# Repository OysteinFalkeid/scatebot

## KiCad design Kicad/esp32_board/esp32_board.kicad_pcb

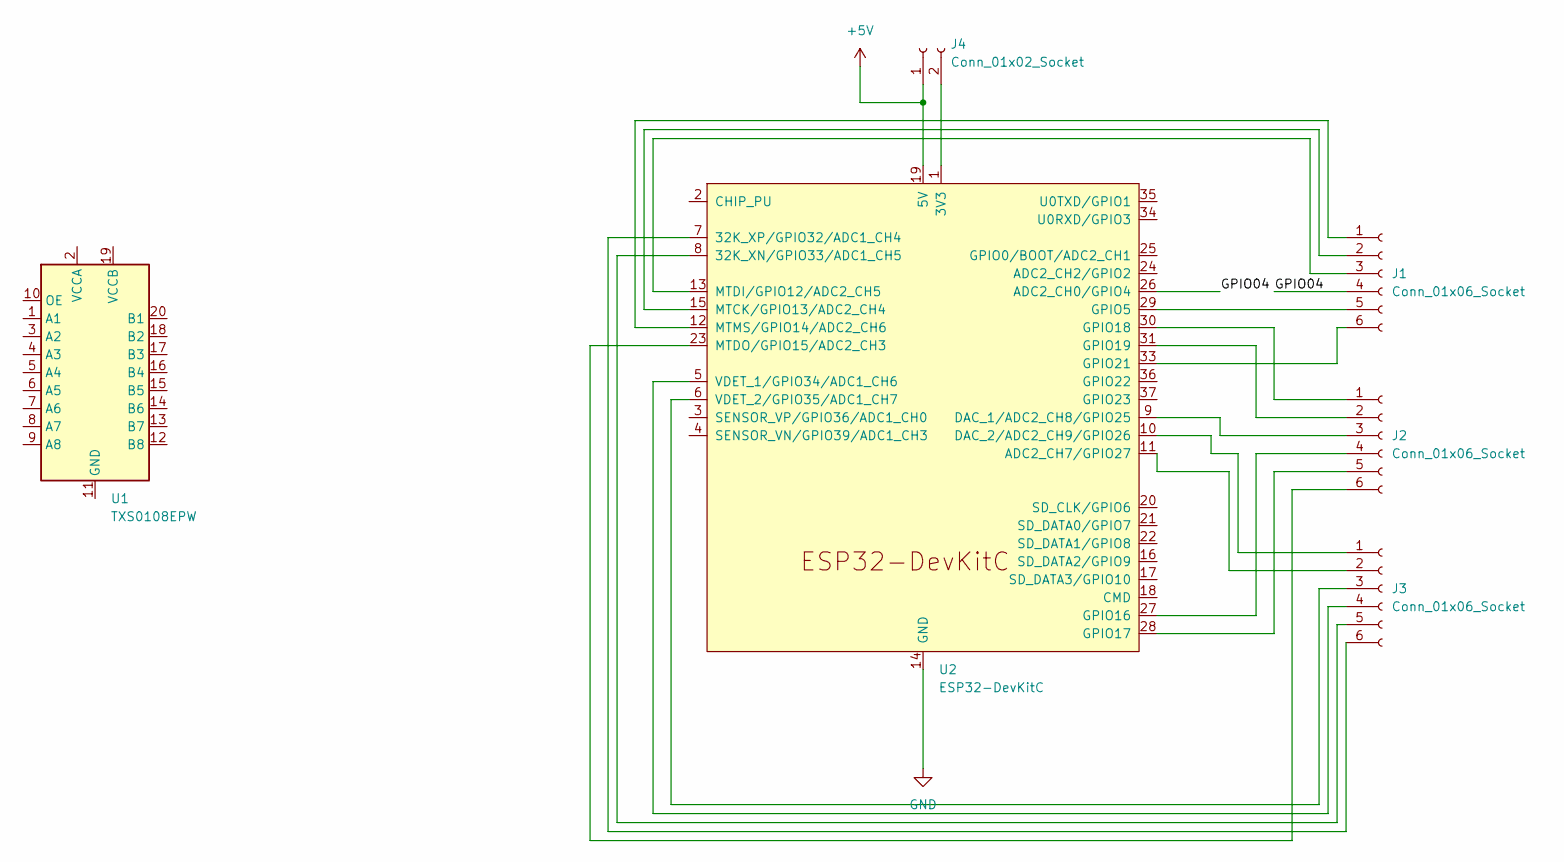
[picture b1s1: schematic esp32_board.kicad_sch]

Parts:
J1, J2, J3: Conn_01x06_Socket; SolderWire-0.75sqmm_1x06_P4.8mm_D1.25mm_OD2.3mm
J4: Conn_01x02_Socket; SolderWire-0.75sqmm_1x02_P4.8mm_D1.25mm_OD2.3mm
U1: TXS0108EPW; TSSOP-20_4.4x6.5mm_P0.65mm
U2: ESP32-DevKitC

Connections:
+5V: J4.1, U2.19 (5V)
/GPIO04: J1.4, U2.26 (ADC2_CH0/GPIO4)
GND: U2.14 (GND), U2.32 (GND), U2.38 (GND)
unnamed: J1.1, U2.12 (MTMS/GPIO14/ADC2_CH6)
unnamed: J1.2, U2.15 (MTCK/GPIO13/ADC2_CH4)
unnamed: J1.3, U2.13 (MTDI/GPIO12/ADC2_CH5)
unnamed: J1.5, U2.29 (GPIO5)
unnamed: J1.6, U2.33 (GPIO21)
unnamed: J2.1, U2.30 (GPIO18)
unnamed: J2.2, U2.31 (GPIO19)
unnamed: J2.3, U2.9 (DAC_1/ADC2_CH8/GPIO25)
unnamed: J2.4, U2.27 (GPIO16)
unnamed: J2.5, U2.28 (GPIO17)
unnamed: J2.6, U2.23 (MTDO/GPIO15/ADC2_CH3)
unnamed: J3.1, U2.10 (DAC_2/ADC2_CH9/GPIO26)
unnamed: J3.2, U2.11 (ADC2_CH7/GPIO27)
unnamed: J3.3, U2.6 (VDET_2/GPIO35/ADC1_CH7)
unnamed: J3.4, U2.5 (VDET_1/GPIO34/ADC1_CH6)
unnamed: J3.5, U2.8 (32K_XN/GPIO33/ADC1_CH5)
unnamed: J3.6, U2.7 (32K_XP/GPIO32/ADC1_CH4)
unnamed: J4.2, U2.1 (3V3)

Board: 2 copper layers, 6 parts (0 on the bottom side), 21 nets, no tracks yet.

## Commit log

2025-05-09 joy package added
2025-05-11 some cleanupp and adding arduino compiler
2025-05-19 twist working
2025-05-20 led driver with game pad
2025-05-22 motor driver missing negative pols
2025-05-25 comutation solved? bad mosfet?
2025-05-29 started on a setup file
2025-05-29 renaming
2025-05-29 creating defines to increase readability
2025-05-29 added hall sens pin
2025-05-29 Add files via upload
    Images of some hardware
2025-05-29 Add files via upload
    Vide of first gamepad test
2025-05-29 cleanup in files and defining function pointers for ISR
2025-05-30 large changes to driver. not tested
2025-05-31 started adding gazebo simulation
2025-06-01 solved some .h file format problems. some problems with variables not changing value
2025-06-02 changes to pwm signal shold reduse noise and large backemp
2025-06-02 fundamental changes to the entire program. redusing interupts and allowing overflow interupt to run inside compare interupt. mosfets are floating evan in pwm low to reduse motor jitter. allowing inte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
2025-06-06 motor pwm seams to work ok. hall sensor readings over uart.
2025-06-06 deleted old unused code
2025-06-06 fixed bug in lcd display
2025-06-11 working mcpwm peripheral on the esp32
2025-06-11 added paths to vs code and started setting upp .h files
2025-06-13 more cleanup and redusing code to functions in seperated files
2025-06-15 testing hall sens to angle functionality
2025-06-17 setting upp a general timer for consistancey
2025-06-20 kicad project started
2025-09-10 uppdate to set compare value to acomodate for angle as input and setting al outputs individualy
